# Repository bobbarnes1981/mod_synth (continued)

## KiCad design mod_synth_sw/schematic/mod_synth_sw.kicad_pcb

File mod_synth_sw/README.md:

Sequential Switch from

http://www.modular.fonik.de/Page32.html

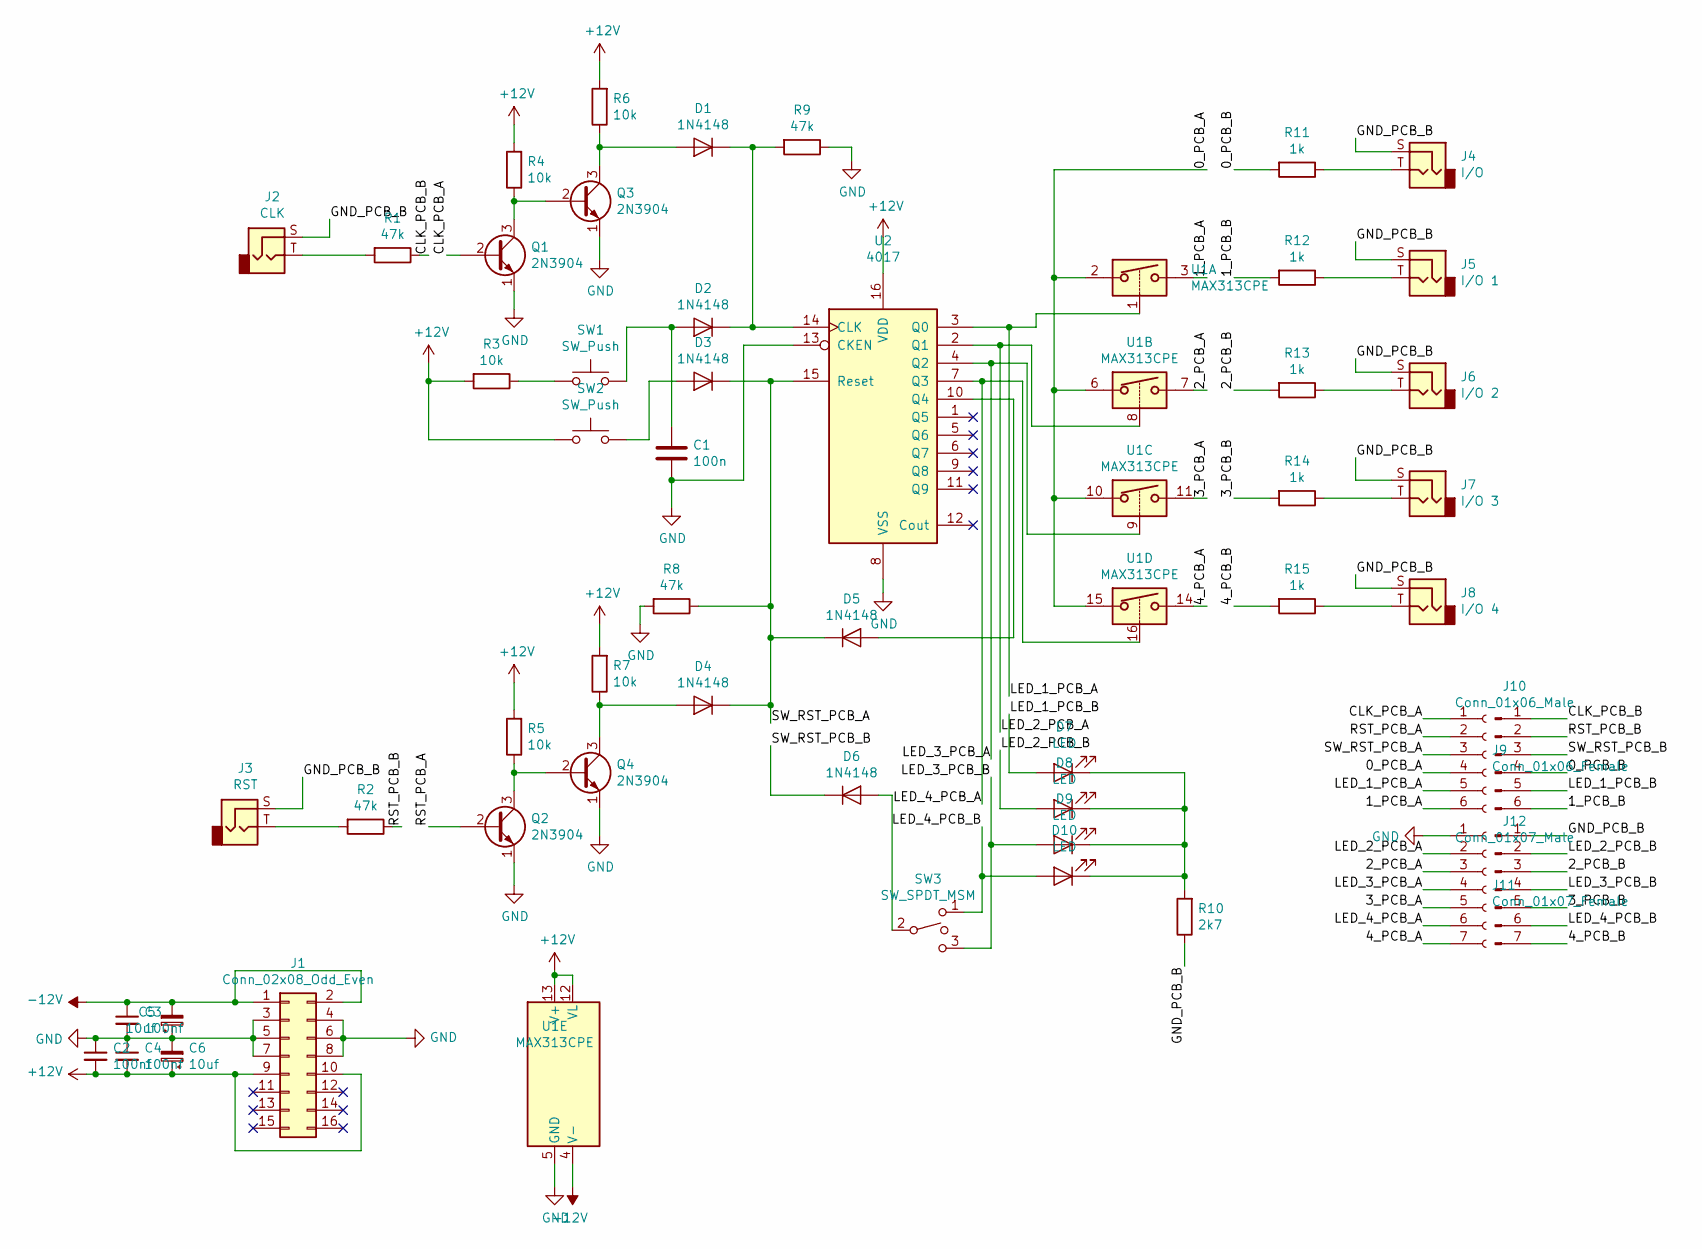
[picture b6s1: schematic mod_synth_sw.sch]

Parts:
C1: 100n; C_Disc_D9.0mm_W2.5mm_P5.00mm
C2, C3, C4: 100nf; C_Disc_D9.0mm_W2.5mm_P5.00mm
C5, C6: 10uf; CP_Radial_D5.0mm_P2.00mm
D1, D2, D3, D4, D5, D6: 1N4148; D_DO-35_SOD27_P7.62mm_Horizontal
D7, D8, D9, D10: LED; LED_D5.0mm
J1: Conn_02x08_Odd_Even; IDC-Header_2x08_P2.54mm_Vertical
J2: CLK; Jack_3.5mm_QingPu_WQP-PJ398SM_Vertical_CircularHoles
J3: RST; Jack_3.5mm_QingPu_WQP-PJ398SM_Vertical_CircularHoles
J4: I/O; Jack_3.5mm_QingPu_WQP-PJ398SM_Vertical_CircularHoles
J5: I/O 1; Jack_3.5mm_QingPu_WQP-PJ398SM_Vertical_CircularHoles
J6: I/O 2; Jack_3.5mm_QingPu_WQP-PJ398SM_Vertical_CircularHoles
J7: I/O 3; Jack_3.5mm_QingPu_WQP-PJ398SM_Vertical_CircularHoles
J8: I/O 4; Jack_3.5mm_QingPu_WQP-PJ398SM_Vertical_CircularHoles
J9: Conn_01x06_Female; PinSocket_1x06_P2.54mm_Vertical
J10: Conn_01x06_Male; PinHeader_1x06_P2.54mm_Vertical
J11: Conn_01x07_Female; PinSocket_1x07_P2.54mm_Vertical
J12: Conn_01x07_Male; PinHeader_1x07_P2.54mm_Vertical
Q1, Q2, Q3, Q4: 2N3904; TO-92_Inline
R1, R2, R8, R9: 47k; R_Axial_DIN0207_L6.3mm_D2.5mm_P10.16mm_Horizontal
R3, R4, R5, R6, R7: 10k; R_Axial_DIN0207_L6.3mm_D2.5mm_P10.16mm_Horizontal
R10: 2k7; R_Axial_DIN0207_L6.3mm_D2.5mm_P10.16mm_Horizontal
R11, R12, R13, R14, R15: 1k; R_Axial_DIN0207_L6.3mm_D2.5mm_P10.16mm_Horizontal
SW1, SW2: SW_Push; PinHeader_1x02_P2.54mm_Vertical
SW3: SW_SPDT_MSM; SPDT_Switch_Vertical
U1: MAX313CPE; DIP-16_W7.62mm_Socket_LongPads
U2: 4017; DIP-16_W7.62mm_Socket_LongPads

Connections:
+12V: C2.2, C4.2, C6.1, J1.9, J1.10, R3.2, R4.2, R5.2, R6.2, R7.2, SW2.1, U1.12 (VL), U1.13 (V+), U2.16 (VDD)
-12V: C3.1, C5.2, J1.1, J1.2, U1.4 (V-)
/0_PCB_A: J9.4, U1.2, U1.6, U1.10, U1.15
/0_PCB_B: J10.4, R11.2
/1_PCB_A: J9.6, U1.3
/1_PCB_B: J10.6, R12.2
/2_PCB_A: J11.3, U1.7
/2_PCB_B: J12.3, R13.2
/3_PCB_A: J11.5, U1.11
/3_PCB_B: J12.5, R14.2
/4_PCB_A: J11.7, U1.14
/4_PCB_B: J12.7, R15.2
/CLK_PCB_A: J9.1, Q1.2 (B)
/CLK_PCB_B: J10.1, R1.1
/GND_PCB_B: J2.S, J3.S, J4.S, J5.S, J6.S, J7.S, J8.S, J12.1, R10.1
/LED_1_PCB_A: J9.5, U1.1, U2.3 (Q0)
/LED_1_PCB_B: D7.2 (A), J10.5
/LED_2_PCB_A: J11.2, U1.8, U2.2 (Q1)
/LED_2_PCB_B: D8.2 (A), J12.2
/LED_3_PCB_A: J11.4, U1.9, U2.4 (Q2)
/LED_3_PCB_B: D9.2 (A), J12.4, SW3.3
/LED_4_PCB_A: J11.6, U1.16, U2.7 (Q3)
/LED_4_PCB_B: D10.2 (A), J12.6, SW3.1
/RST_PCB_A: J9.2, Q2.2 (B)
/RST_PCB_B: J10.2, R2.1
/SW_RST_PCB_A: D3.1 (K), D4.1 (K), D5.1 (K), J9.3, R8.1, U2.15 (Reset)
/SW_RST_PCB_B: D6.1 (K), J10.3
GND: C1.2, C2.1, C3.2, C4.1, C5.1, C6.2, J1.3, J1.4, J1.5, J1.6, J1.7, J1.8, J11.1, Q1.1 (E), Q2.1 (E), Q3.1 (E), Q4.1 (E), R8.2, R9.1, U1.5 (GND), U2.8 (VSS), U2.13 (CKEN)
unnamed: C1.1, D2.2 (A), SW1.2
unnamed: D1.1 (K), D2.1 (K), R9.2, U2.14 (CLK)
unnamed: D1.2 (A), Q3.3 (C), R6.1
unnamed: D3.2 (A), SW2.2
unnamed: D4.2 (A), Q4.3 (C), R7.1
unnamed: D5.2 (A), U2.10 (Q4)
unnamed: D6.2 (A), SW3.2
unnamed: D7.1 (K), D8.1 (K), D9.1 (K), D10.1 (K), R10.2
unnamed: J2.T, R1.2
unnamed: J3.T, R2.2
unnamed: J4.T, R11.1
unnamed: J5.T, R12.1
unnamed: J6.T, R13.1
unnamed: J7.T, R14.1
unnamed: J8.T, R15.1
unnamed: Q1.3 (C), Q3.2 (B), R4.1
unnamed: Q2.3 (C), Q4.2 (B), R5.1
unnamed: R3.1, SW1.1

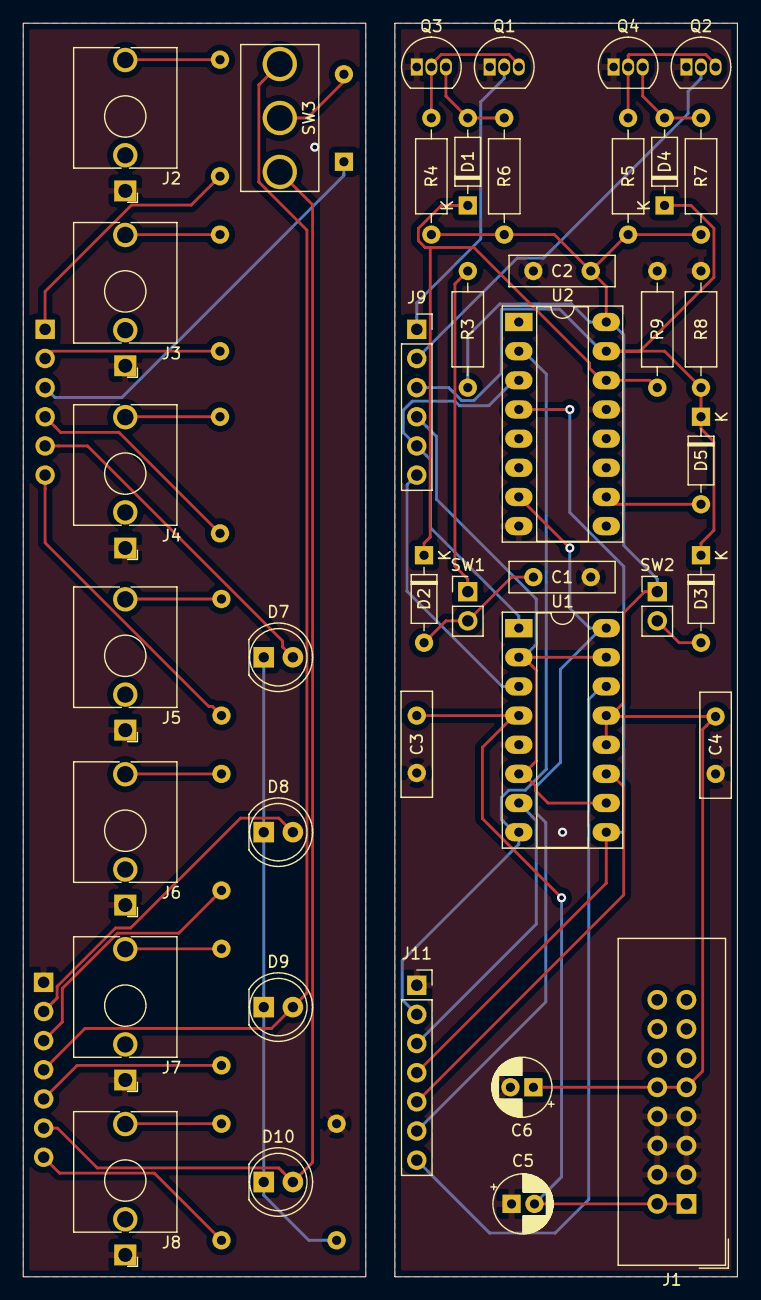
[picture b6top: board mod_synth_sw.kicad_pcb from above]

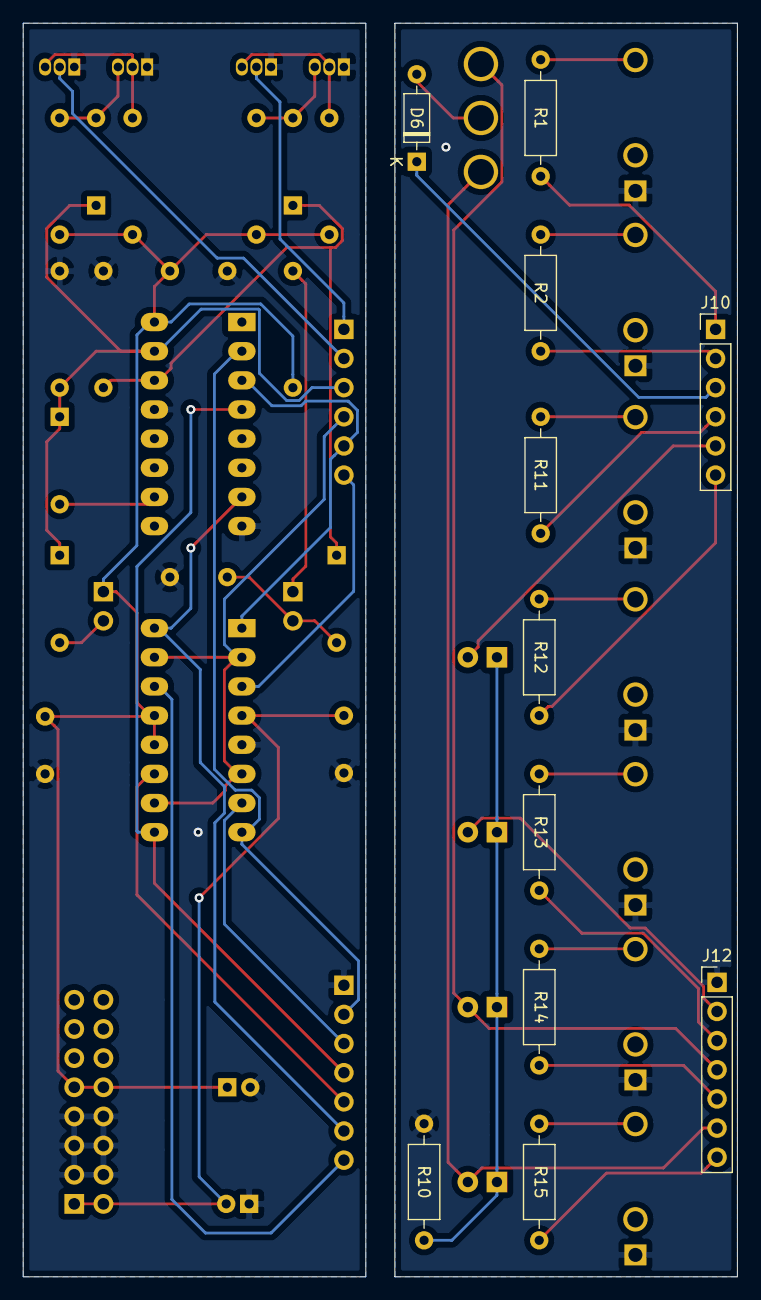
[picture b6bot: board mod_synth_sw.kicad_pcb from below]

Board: 2 copper layers, 62.2 x 109.2 mm, 52 parts (11 on the bottom side), 46 nets.

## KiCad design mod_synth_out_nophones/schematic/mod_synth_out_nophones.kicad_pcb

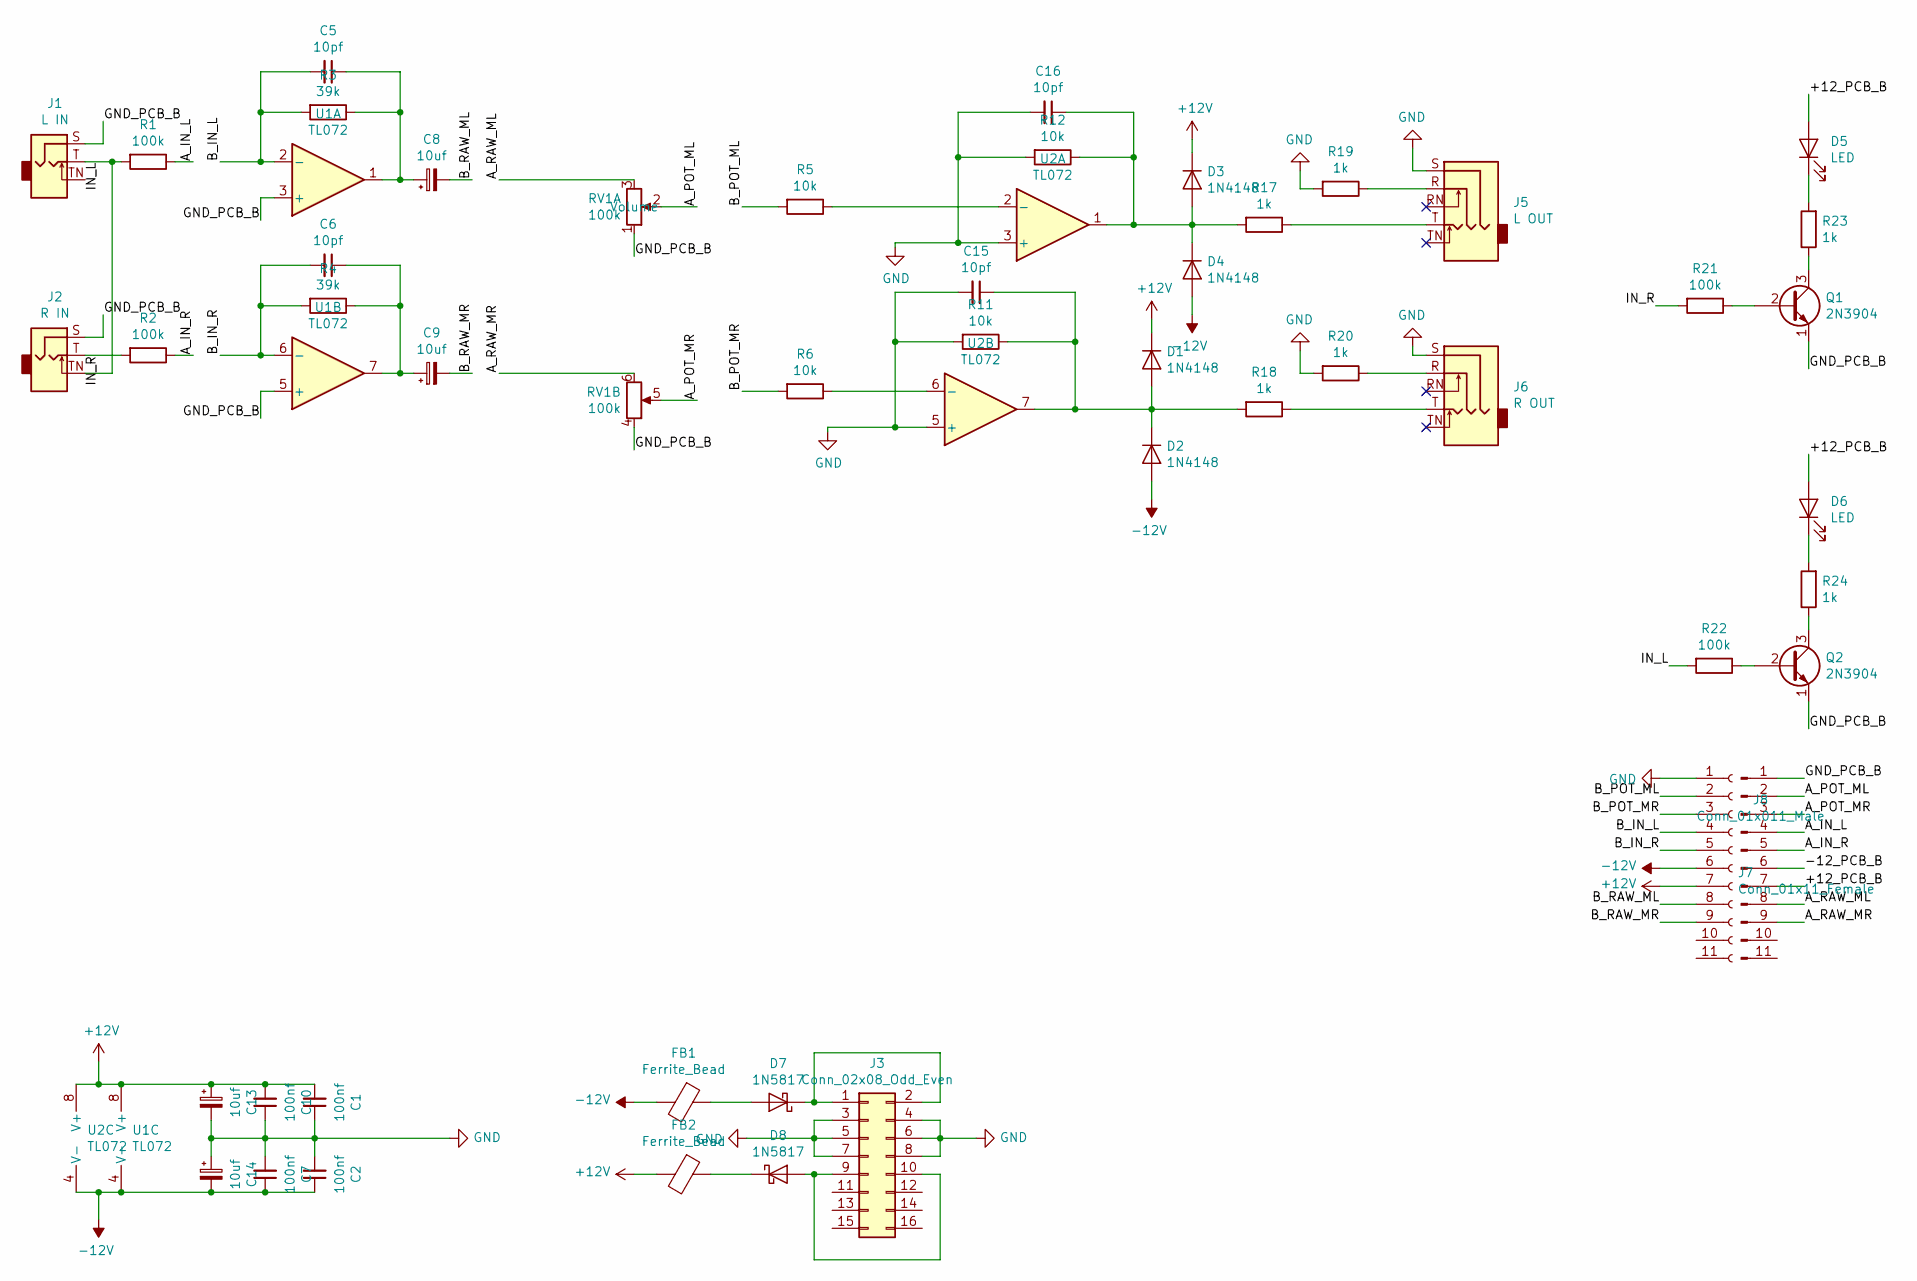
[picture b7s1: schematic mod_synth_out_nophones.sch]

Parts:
C1, C2, C7, C10: 100nf; C_Disc_D9.0mm_W2.5mm_P5.00mm
C5, C6, C15, C16: 10pf; C_Disc_D9.0mm_W2.5mm_P5.00mm
C8, C9, C13, C14: 10uf; CP_Radial_D5.0mm_P2.00mm
D1, D2, D3, D4: 1N4148; D_DO-35_SOD27_P7.62mm_Horizontal
D5, D6: LED; LED_D5.0mm
D7, D8: 1N5817; D_DO-41_SOD81_P10.16mm_Horizontal
FB1, FB2: Ferrite_Bead; R_Axial_DIN0207_L6.3mm_D2.5mm_P10.16mm_Horizontal
J1: L IN; Jack_3.5mm_QingPu_WQP-PJ398SM_Vertical_CircularHoles
J2: R IN; Jack_3.5mm_QingPu_WQP-PJ398SM_Vertical_CircularHoles
J3: Conn_02x08_Odd_Even; IDC-Header_2x08_P2.54mm_Vertical
J5: L OUT; WQP-PJ612A-A
J6: R OUT; WQP-PJ612A-A
J7: Conn_01x11_Female; PinSocket_1x11_P2.54mm_Vertical
J8: Conn_01x011_Male; PinHeader_1x11_P2.54mm_Vertical
Q1, Q2: 2N3904; TO-92_Inline
R1, R2, R21, R22: 100k; R_Axial_DIN0207_L6.3mm_D2.5mm_P10.16mm_Horizontal
R3, R4: 39k; R_Axial_DIN0207_L6.3mm_D2.5mm_P10.16mm_Horizontal
R5, R6, R11, R12: 10k; R_Axial_DIN0207_L6.3mm_D2.5mm_P10.16mm_Horizontal
R17, R18, R19, R20, R23, R24: 1k; R_Axial_DIN0207_L6.3mm_D2.5mm_P10.16mm_Horizontal
RV1: 100k; Potentiometer_Alpha_RD902F-40-00D_Dual_Vertical_CircularHol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
U1, U2: TL072; DIP-8_W7.62mm_Socket_LongPads

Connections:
+12V: C1.2, C10.2, C13.1, D1.1 (K), D3.1 (K), FB2.2, J7.7, U1.8 (V+), U2.8 (V+)
-12V: C2.1, C7.1, C14.2, D2.2 (A), D4.2 (A), FB1.2, J7.6, U1.4 (V-), U2.4 (V-)
/+12_PCB_B: D5.2 (A), D6.2 (A), J8.7
/-12_PCB_B: J8.6
/A_IN_L: J8.4, R1.1
/A_IN_R: J8.5, R2.1
/A_POT_ML: J8.2, RV1.2
/A_POT_MR: J8.3, RV1.5
/A_RAW_ML: J8.8, RV1.3
/A_RAW_MR: J8.9, RV1.6
/B_IN_L: C5.2, J7.4, R3.2, U1.2 (-)
/B_IN_R: C6.2, J7.5, R4.2, U1.6 (-)
/B_POT_ML: J7.2, R5.2
/B_POT_MR: J7.3, R6.2
/B_RAW_ML: C8.2, J7.8
/B_RAW_MR: C9.2, J7.9
/GND_PCB_B: J1.S, J2.S, J8.1, Q1.1 (E), Q2.1 (E), RV1.1, RV1.4, U1.3 (+), U1.5 (+)
/IN_L: J1.T, J2.TN, R1.2, R22.2
/IN_R: J2.T, R2.2, R21.2
GND: C1.1, C2.2, C7.2, C10.1, C13.2, C14.1, C15.2, C16.2, J3.3, J3.4, J3.5, J3.6, J3.7, J3.8, J5.S, J6.S, J7.1, R11.2, R12.2, R19.2, R20.2, U2.3 (+), U2.5 (+)
unnamed: C5.1, C8.1, R3.1, U1.1
unnamed: C6.1, C9.1, R4.1, U1.7
unnamed: C15.1, D1.2 (A), D2.1 (K), R11.1, R18.2, U2.7
unnamed: C16.1, D3.2 (A), D4.1 (K), R12.1, R17.2, U2.1
unnamed: D5.1 (K), R23.2
unnamed: D6.1 (K), R24.2
unnamed: D7.1 (K), J3.1, J3.2
unnamed: D7.2 (A), FB1.1
unnamed: D8.1 (K), FB2.1
unnamed: D8.2 (A), J3.9, J3.10
unnamed: J5.R, R19.1
unnamed: J5.T, R17.1
unnamed: J6.R, R20.1
unnamed: J6.T, R18.1
unnamed: Q1.2 (B), R21.1
unnamed: Q1.3 (C), R23.1
unnamed: Q2.2 (B), R22.1
unnamed: Q2.3 (C), R24.1
unnamed: R5.1, U2.2 (-)
unnamed: R6.1, U2.6 (-)

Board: 2 copper layers, 50 parts (42 on the bottom side), 39 nets, no tracks yet.

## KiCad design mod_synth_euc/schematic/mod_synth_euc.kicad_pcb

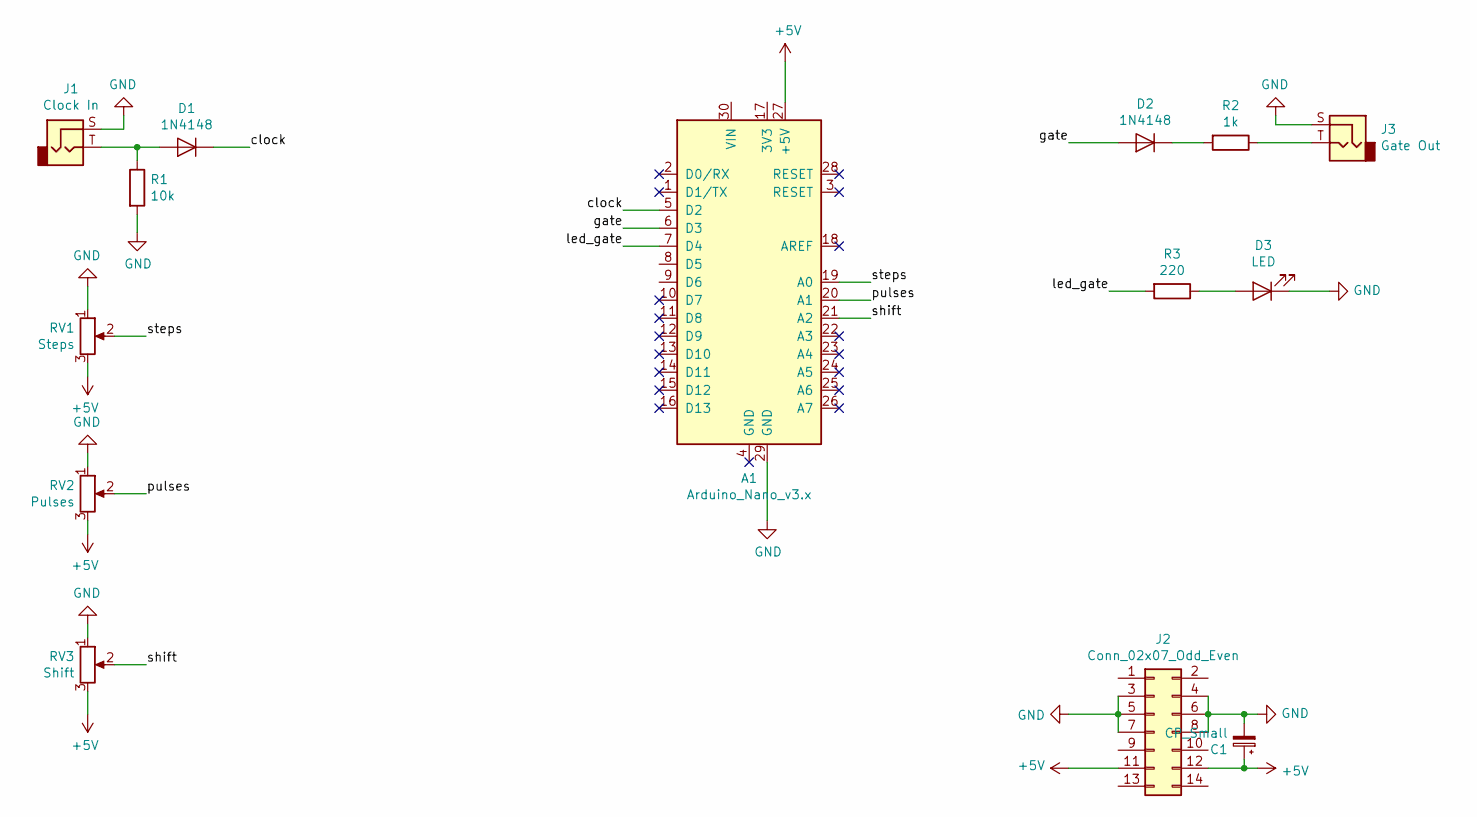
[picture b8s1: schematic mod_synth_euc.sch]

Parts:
A1: Arduino_Nano_v3.x; Arduino_Nano
C1: CP_Small; CP_Radial_D5.0mm_P2.00mm
D1, D2: 1N4148; D_DO-35_SOD27_P7.62mm_Horizontal
D3: LED; LED_D5.0mm
J1: Clock In; Jack_3.5mm_QingPu_WQP-PJ398SM_Vertical_CircularHoles
J2: Conn_02x07_Odd_Even; IDC-Header_2x07_P2.54mm_Vertical
J3: Gate Out; Jack_3.5mm_QingPu_WQP-PJ398SM_Vertical_CircularHoles
R1: 10k; R_Axial_DIN0207_L6.3mm_D2.5mm_P10.16mm_Horizontal
R2: 1k; R_Axial_DIN0207_L6.3mm_D2.5mm_P10.16mm_Horizontal
R3: 220; R_Axial_DIN0207_L6.3mm_D2.5mm_P10.16mm_Horizontal
RV1: Steps; Potentiometer_Alpha_RD901F-40-00D_Single_Vertical_CircularH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
RV2: Pulses; Potentiometer_Alpha_RD901F-40-00D_Single_Vertical_CircularH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
RV3: Shift; Potentiometer_Alpha_RD901F-40-00D_Single_Vertical_CircularH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

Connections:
+5V: A1.27 (+5V), C1.1, J2.11, J2.12, RV1.3, RV2.3, RV3.3
/clock: A1.5 (D2), D1.1 (K)
/gate: A1.6 (D3), D2.2 (A)
/led_gate: A1.7 (D4), R3.2
/pulses: A1.20 (A1), RV2.2
/shift: A1.21 (A2), RV3.2
/steps: A1.19 (A0), RV1.2
GND: A1.29 (GND), C1.2, D3.1 (K), J1.S, J2.3, J2.4, J2.5, J2.6, J2.7, J2.8, J3.S, R1.2, RV1.1, RV2.1, RV3.1
unnamed: D1.2 (A), J1.T, R1.1
unnamed: D2.1 (K), R2.2
unnamed: D3.2 (A), R3.1
unnamed: J3.T, R2.1

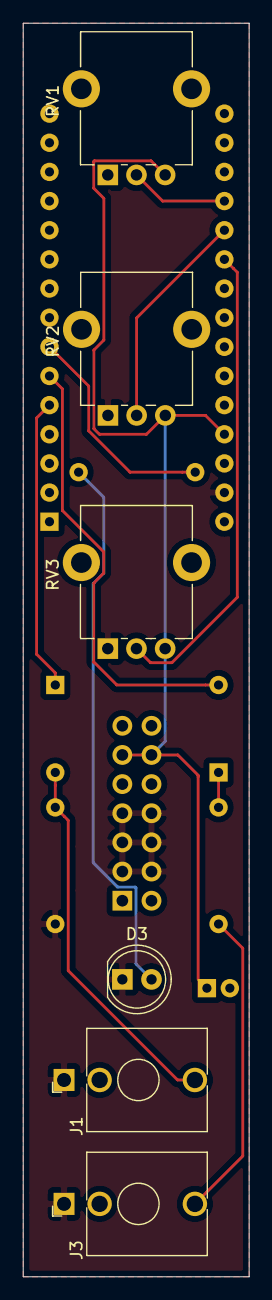
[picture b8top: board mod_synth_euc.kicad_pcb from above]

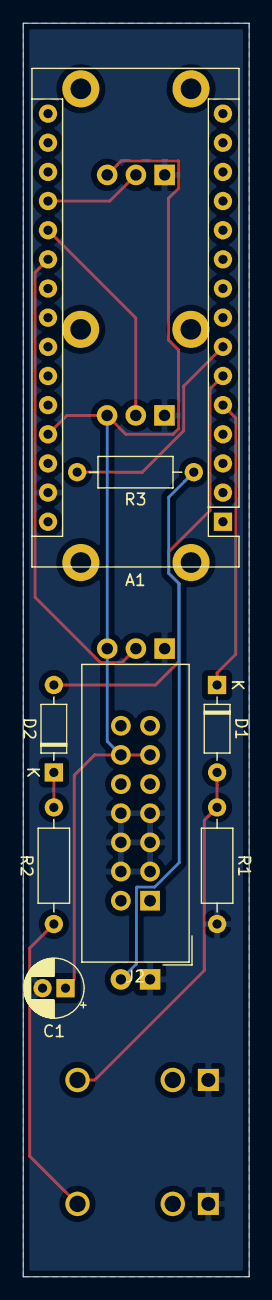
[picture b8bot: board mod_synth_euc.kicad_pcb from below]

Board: 2 copper layers, 19.7 x 109.2 mm, 14 parts (8 on the bottom side), 12 nets.

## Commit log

2019-06-26 Added synth clock initial code
2019-06-26 Addedd synth sequencer initial code
2019-06-29 Simplify setup
2019-06-29 Implement gate and reset features
2019-06-29 Add partial schematic
2019-06-29 Fix paths for Arduino IDE
2019-06-29 Finish schematic for seq and add schematic for clk
2019-06-30 Add exported schematics
2019-07-02 Add initial schematic for VCO and some readmes
2019-07-02 Update schematic for vco
2019-07-02 Remove debug code
2019-07-02 Add external LED
2019-07-03 Remove pull-down resistor from gate output
2019-07-03 Add labels and cleanup square/PWM section
2019-07-03 Update schematic images
2019-07-03 Add empty projects for lpf and envelope
2019-07-03 Respond to reset immediately
2019-07-03 Revert commit. Reset after current step
2019-07-04 Add footprints to seq for AlphPot and EurorackJack
2019-07-04 Start to layout seq PCB
2019-07-04 Rough layout for seq
2019-07-04 Add 3u 28hp dimensions to seq
2019-07-04 Start to reorganise layout
2019-07-04 Attempt to lay some tracks
2019-07-04 Running out of places for tracks
2019-07-05 Add pcb size for clock
2019-07-05 Add labels for PCB resize for sequencer
2019-07-05 Update layouts
2019-07-05 Layout clock board
2019-07-05 Generate gerber files
2019-07-05 Some PCB layout for VCO
2019-07-05 Layout PCB
2019-07-05 Shorten clock PCB to 109mm
2019-07-05 Shorten VCO PCB without altering layout yet
2019-07-05 Remove out of date images and gerber files
2019-07-05 Update PCB layouts
2019-07-05 Increase max BPM x4
2019-07-05 Update envelope schematic
2019-07-05 Add some footprints
2019-07-05 Add footprints
2019-07-06 Add panel layout
2019-07-07 Anodized aluminium is cheaper
2019-07-07 Make gate max 1 second
2019-07-08 Add possible PCB front panel
2019-07-08 Backup
2019-07-08 Start work on envelope PCB
2019-07-08 Add dual pcb for envelope
2019-07-09 Move pcbs closer (0.1")
2019-07-09 Add footprint for SPDT mini toggle switch
2019-07-09 Rework to add mounting point
2019-07-09 Very rough outline of seq PCB
2019-07-09 Update schematic
2019-07-09 Add schematic for filter
2019-07-10 Add some footprints to LPF
2019-07-10 Add datasheets
2019-07-10 Add switch footprints
2019-07-10 Update footprint for env
2019-07-10 Recreate tracks near switch
2019-07-10 Organise schematic and cram components on PCB
2019-07-10 Try to clean up layout
2019-07-11 Layout first PCB
2019-07-11 Layout 6hp board
2019-07-16 Add folder for divider
2019-07-16 Time clock peaks and use to calculate gate as percentage
2019-07-23 Reverse pulse width knob and CV level
2019-07-24 Connect J1 to GND
2019-07-24 Move labels for resistors to avoid confusion
2019-07-25 Move PCB labels
2019-07-25 Update READMEs with references to Look Mum No Computer
2019-07-25 Flip components
2019-07-25 Sequencer board layout
2019-07-25 Finish sequencer
2019-07-26 Start schematic for VCA
2019-07-26 Add more components to schematic
2019-07-26 Complete schematic for single input vca
2019-07-26 Move folder and add pcb connector
2019-07-26 Modify pcb layout
2019-07-27 Layout PCB for VCA
2019-07-27 Add support for top of PCB, add folder for kick
2019-07-28 Initial ideas for smaller sequencer
2019-08-10 Add missing +12v to U1
2019-08-10 Re-add missing mounting hole
2019-08-11 Volume resistor should be 20k
2019-08-11 Add missing connector
2019-08-12 Use 16 pin socket for 16 pin device
2019-08-12 Update PCB to use 16 pin socket
2019-08-14 Remove gate from smaller sequencer
2019-08-14 Layout PCB for seq_1
2019-08-14 Centre connector, add arduino code
2019-08-14 Buffered multiple from skullandcircuits
2019-08-14 Add empty project for mix
2019-08-15 Move LEDs
2019-08-15 Draw schematic
2019-08-15 Update mixer
2019-08-15 Change potentiometer pads
2019-08-15 Update multiple
2019-08-15 Recreate schematic from Skullandcircuits
2019-08-15 Add attribution
2019-08-16 Add footprints and values
2019-08-16 Remove PCB front panel
2019-08-16 Attempt to layout PCB
2019-08-16 Remove ramp and sin outputs
2019-08-16 Add dummy folders for output and quantizer
2019-08-17 Add surface mount LFO
2019-08-17 layout clock divider pcb
2019-08-17 Add PCB connectors
2019-08-17 Layout tracks for divider
2019-08-17 Rotate connector
2019-08-17 Move component labels
2019-08-18 Add schematic for sequential switch
2019-08-18 Group some components in PCB
2019-08-18 Layout some tracks
2019-08-18 Enlarge second PCB
2019-08-18 Complete PCB layout
2019-08-18 Add missing connections
2019-08-19 Convert SMT LFO to multi-PCB
2019-08-19 Possible three PCB layout
2019-08-19 Re-add SMT LFO to attmept multi-PCB layout
2019-08-19 Alter PCB layouts
2019-08-19 Add panel oulines SVG
2019-08-20 Add details for clock panel
2019-08-20 Create CSV to calculate panel layouts
2019-08-20 Add labels to panel mock up
2019-08-21 Layout some of VCA panel
2019-08-21 Draw kick schematic
2019-08-21 Initial work on arduino gate sequencer
2019-08-21 Add decoupling for op amp
2019-08-21 Rename ino file
2019-08-22 Layout and add LED to Kick
2019-08-22 re-add VCA support pins
2019-08-23 Fix resistor location
2019-08-23 Add quantizer from Barton
2019-08-23 Adjust clock range, implement initial quantizer
2019-08-23 Add todo
2019-08-24 Update schematic and code
2019-08-24 Add method for 24 bit quantize
2019-08-24 Add scales
2019-08-24 comments
2019-08-24 Add notes
2019-08-25 Use defines instead of variables
2019-08-25 Add scale/note input and led output
2019-08-25 Debug logging
2019-08-25 disable logging for non-debug
2019-08-25 Return correct index for note/scale
2019-08-25 Improve code, start PCB layout
2019-08-25 finish layout
2019-08-25 Use 3mm LEDs for panel hole clearance
2019-08-25 Flash LED when showing settings
2019-08-26 CHoose lower note if less than higher one so 'zero' is more reliable
2019-08-26 Fix header, allow sharps, 10 bit not 24!
2019-08-26 Move arduino code
2019-08-26 Add code for euclidean gate generator
2019-08-26 Use correct value for analog max
2019-08-26 Add rough schematic for euclidean rhythms
2019-08-27 Add indicator leds, update firmware to match schematic
2019-08-27 Turn off led when no steps/pulses selected
2019-08-27 Add offset input, flash x/second, add output pulse width
2019-08-27 Attempt PCB layout for euclidean rhythms
2019-08-27 Remove steps/pulses LEDs for one PCB
2019-08-27 Reduce max steps
2019-08-28 Attempt to remove delay and dejitter analog reads
2019-08-28 Attempt to dejitter analog reads
2019-08-28 Update ignore values, change connector on euclid
2019-08-29 Initial commit for Output
2019-08-29 Initial clone of befaco (without cue)
2019-08-29 Attempt layout of output with through hole devices
2019-08-29 Update resistor options
2019-08-29 Attmept layout of output pcb on large pcb
2019-08-30 Finish huge output pcb
2019-08-30 Align headphone output
2019-08-30 Rough idea for simple output
2019-08-30 Layout components
2019-08-30 Move to work in progress folder
2019-08-31 Update values
2019-08-31 Fix reversed capacitor
2019-08-31 Add passive attenuator
2019-09-01 Add simple noise snare/hihat
2019-09-02 Align front panel components
2019-09-02 Add components for ADSR
2019-09-03 Remove switch
2019-09-03 Move to sub modules
2019-09-03 Update sub module
2019-09-05 Reverse pots
2019-09-05 Use correct size socket
2019-09-27 Fix crosstalk on analog read
